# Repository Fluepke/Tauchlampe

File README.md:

Tauchlampe
==========

Die Dokumentation dieses Projektes finden Sie in der entsprechenden [Wiki](https://github.com/Fluepke/Tauchlampe/wiki)

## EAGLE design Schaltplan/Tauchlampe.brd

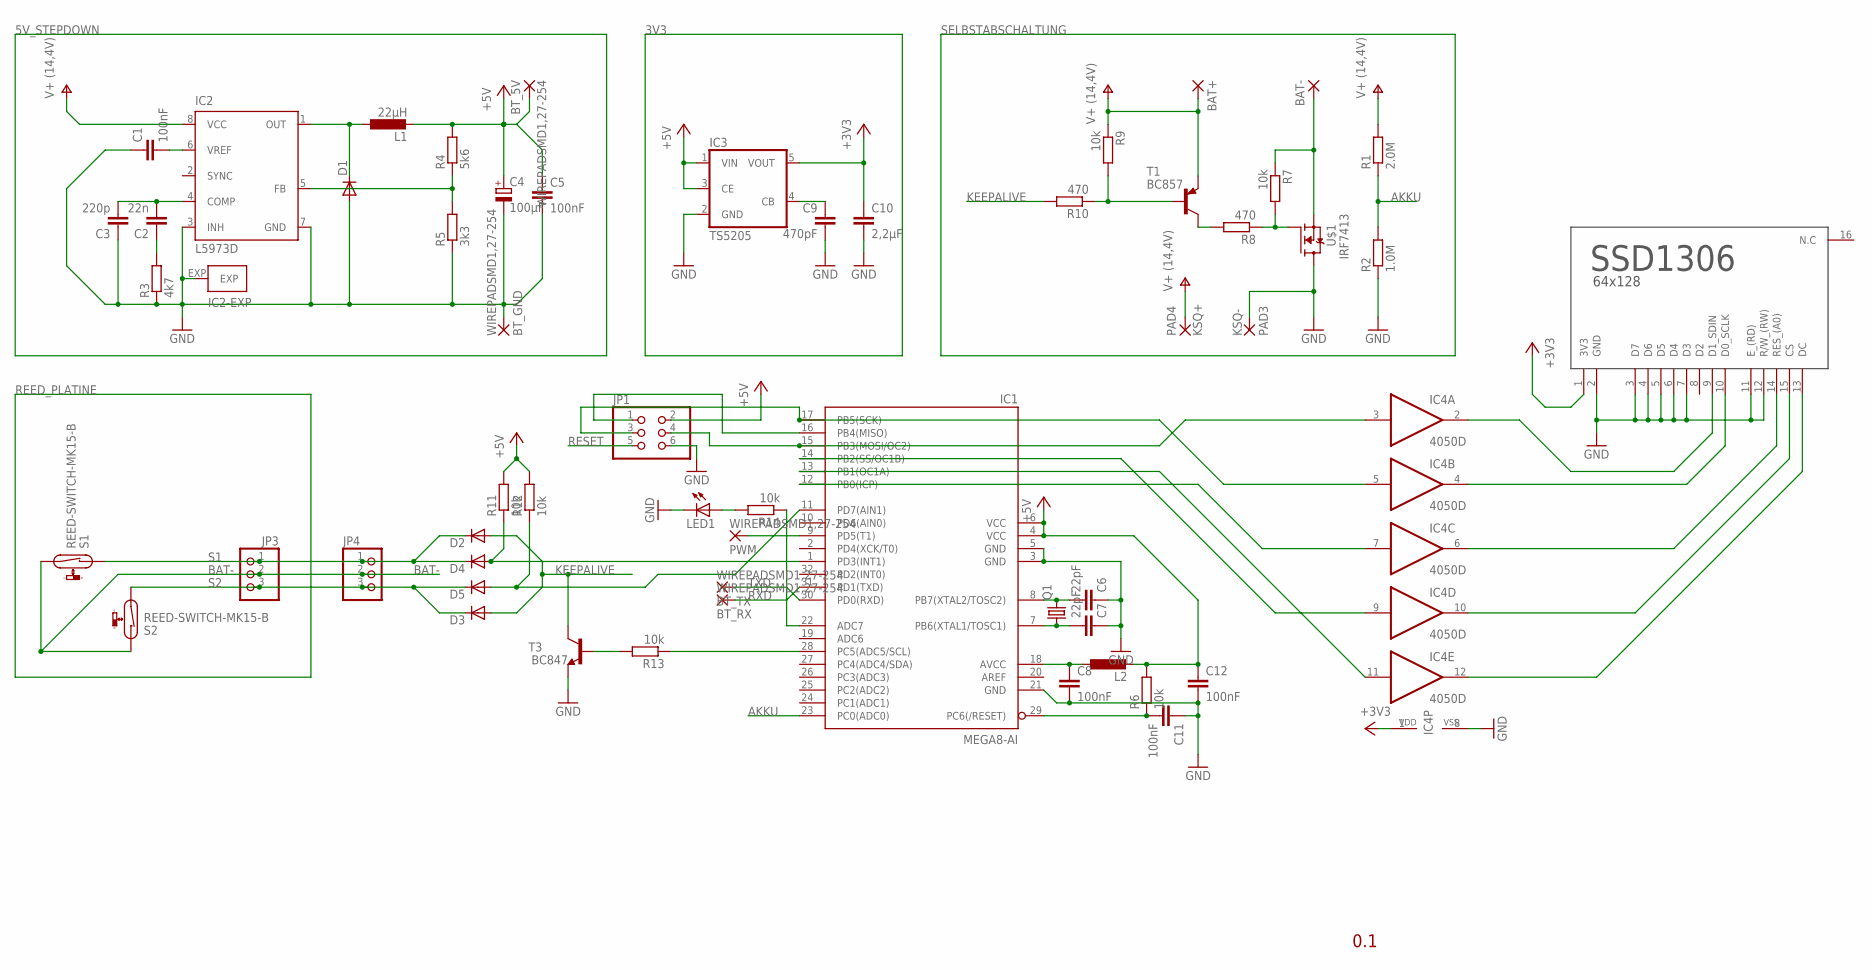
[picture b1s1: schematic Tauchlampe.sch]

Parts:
BAT+: WIREPAD3,81/1,1; 3,81/1,1
BAT-: WIREPAD3,81/1,1; 3,81/1,1
BT_5V: WIREPADSMD1,27-254; SMD1,27-2,54
BT_GND: WIREPADSMD1,27-254; SMD1,27-2,54
BT_RX: WIREPADSMD1,27-254; SMD1,27-2,54
BT_TX: WIREPADSMD1,27-254; SMD1,27-2,54
C1, C8, C11, C12: 100nF; C0603K
C2: 22n; C0603K
C3: 220p; C0603K
C4: 100µF; 153CLV-0505
C5: 100nF; C1206
C6, C7: 22pF; C1206
C9: 470pF; C0603
C10: 2,2µF; C0603
D1: DIODE-SMB; SMB
D2, D3, D4, D5: DIODE-SOD323-W; SOD323-W
IC1: MEGA8-AI; TQFP32-08
IC2: L5973D; HSOP8
IC3: TS5205; SOT25
IC4: 4050D; SO16
JP1: PINHD-2X3; 2X03
JP3, JP4: PINHD-1X03_2.54; 1X03
L1: 22µH; PISG
L2: L-EUL2012C; L2012C
LED1: LEDCHIP-LED0805; CHIP-LED0805
PAD3: KSQ-; 3,81/1,1
PAD4: KSQ+; 3,81/1,1
PWM: WIREPADSMD1,27-254; SMD1,27-2,54
Q1: CRYSTALHC49UP; HC49UP
R1: 2.0M; M1206
R2: 1.0M; M1206
R3: 4k7; R0603
R4: 5k6; R0603
R5: 3k3; R0603
R6: 10k; R1206
R7, R9, R14: 10k; M0805
R8, R10: 470; M0805
R11, R12, R13: 10k; M1206
S1, S2: REED-SWITCH-MK15-B; MK15
T1: BC857; SOT23-BEC
T3: BC847; SOT23
U$1: IRF7413; SO-8
U$2: SDD1306; 2X08

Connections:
+3V3: C10.1, IC3.5 (VOUT), IC4.1 (VDD), U$2.1 (3V3)
+5V: BT_5V.1, C4.+, C5.1, C12.1, IC1.4 (VCC), IC1.6 (VCC), IC3.1 (VIN), IC3.3 (CE), JP1.2, L1.2, L2.2, R4.2, R6.2, R11.2, R12.2
AKKU: IC1.23 (PC0(ADC0)), R1.1, R2.2
BAT-: BAT-.1, JP3.2, JP4.2, R7.1, S1.2, S2.1, U$1.1 (S), U$1.2 (S), U$1.3 (S)
CS_5V: IC1.14 (PB2(SS/OC1B)), IC4.9 (I)
D0_SCLK_5V: IC1.17 (PB5(SCK)), IC4.5 (I), JP1.3
D1_SDIN_5V: IC1.15 (PB3(MOSI/OC2)), IC4.3 (I), JP1.4
DC_5V: IC1.13 (PB1(OC1A)), IC4.11 (I)
GND: BT_GND.1, C1.1, C3.1, C4.-, C5.2, C6.1, C7.1, C8.2, C9.2, C10.2, C11.1, C12.2, D1.A, IC1.3 (GND), IC1.5 (GND), IC1.21 (GND), IC2.3 (INH), IC2.7 (GND), IC2.EXP, IC3.2 (GND), IC4.8 (VSS), JP1.6, LED1.C, PAD3.1, R2.1, R3.1, R5.1, T3.2 (E), U$1.5 (D), U$1.6 (D), U$1.7 (D), U$1.8 (D), U$2.2 (GND), U$2.3 (D7), U$2.4 (D6), U$2.5 (D5), U$2.6 (D4), U$2.7 (D3), U$2.11 (E_(RD)), U$2.12 (R/W_(RW))
KEEPALIVE: D2.A, D3.A, R10.2, T3.3 (C)
unnamed: C1.2, IC2.6 (VREF)
unnamed: D4.A, IC1.1 (PD3(INT1)), R11.1
unnamed: C2.2, C3.2, IC2.4 (COMP)
unnamed: C2.1, R3.2
unnamed: D1.C, IC2.1 (OUT), L1.1
unnamed: C6.2, IC1.8 (PB7(XTAL2/TOSC2)), Q1.2
unnamed: IC2.5 (FB), R4.1, R5.2
unnamed: C7.2, IC1.7 (PB6(XTAL1/TOSC1)), Q1.1
unnamed: R7.2, R8.1, U$1.4 (G)
unnamed: R9.2, R10.1, T1.B
unnamed: R8.2, T1.C
unnamed: D5.A, IC1.11 (PD7(AIN1)), R12.1
unnamed: R13.2, T3.1 (B)
unnamed: IC1.16 (PB4(MISO)), JP1.1
unnamed: IC1.28 (PC5(ADC5/SCL)), R13.1
unnamed: C9.1, IC3.4 (CB)
unnamed: C8.1, IC1.18 (AVCC), L2.1
unnamed: IC4.2 (O), U$2.9 (D1_SDIN)
unnamed: IC4.4 (O), U$2.10 (D0_SCLK)
unnamed: IC4.6 (O), U$2.14 (RES_(A0))
unnamed: IC4.10 (O), U$2.15 (CS)
unnamed: IC4.12 (O), U$2.13 (DC)
unnamed: IC1.9 (PD5(T1)), PWM.1
unnamed: LED1.A, R14.2
unnamed: IC1.22 (ADC7), R14.1
RESET: C11.2, IC1.29 (PC6(/RESET)), JP1.5, R6.1
RES_5V: IC1.12 (PB0(ICP)), IC4.7 (I)
RXD: BT_RX.1, IC1.31 (PD1(TXD))
S1: D2.C, D4.C, JP3.1, JP4.1, S1.1
S2: D3.C, D5.C, JP3.3, JP4.3, S2.2
TXD: BT_TX.1, IC1.30 (PD0(RXD))
V+: BAT+.1, IC2.8 (VCC), PAD4.1, R1.2, R9.1, T1.E

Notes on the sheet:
0.1

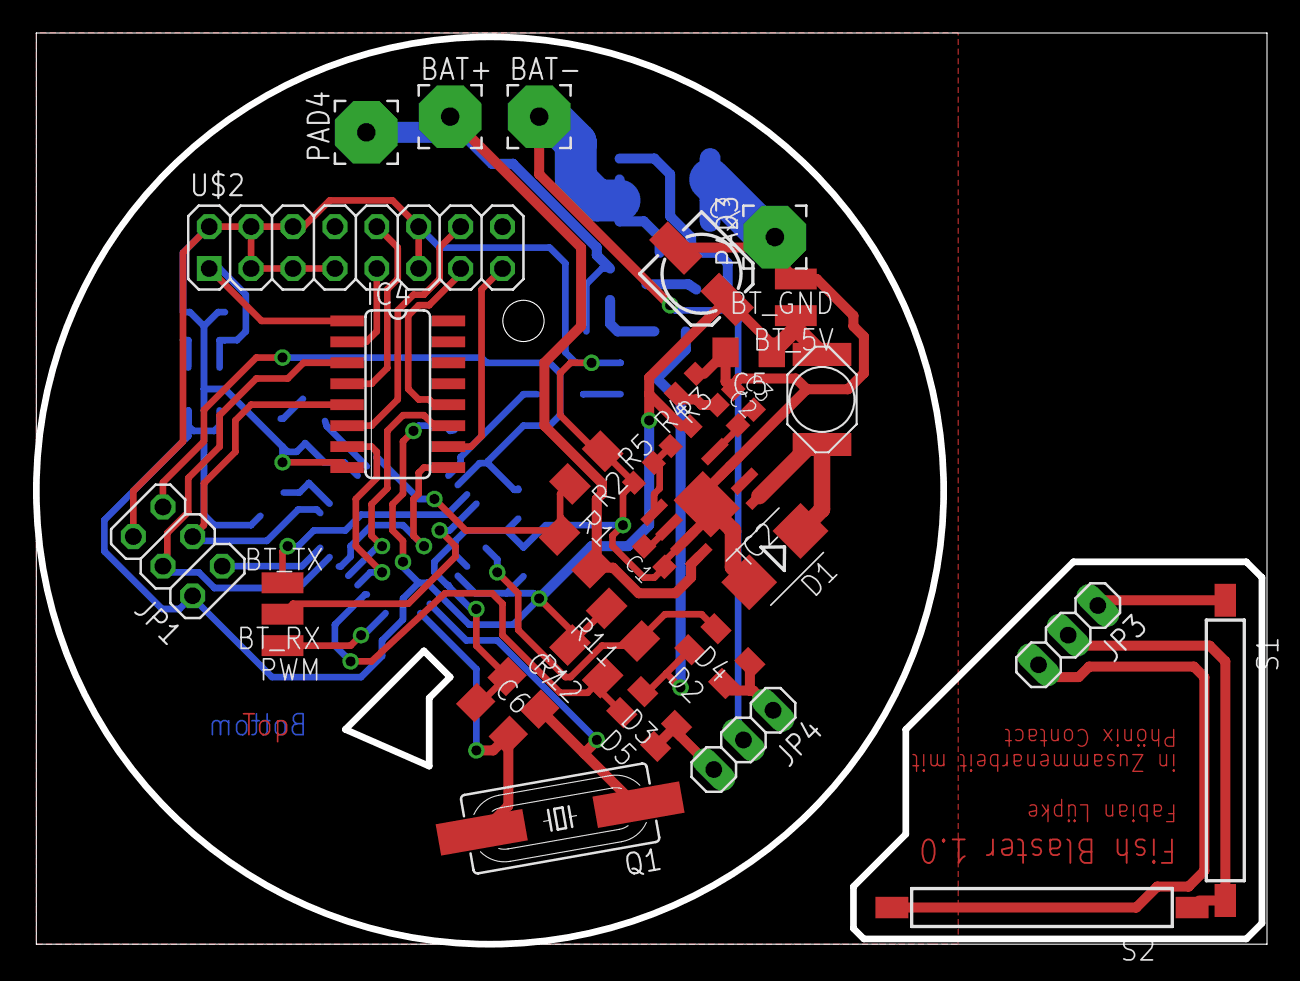
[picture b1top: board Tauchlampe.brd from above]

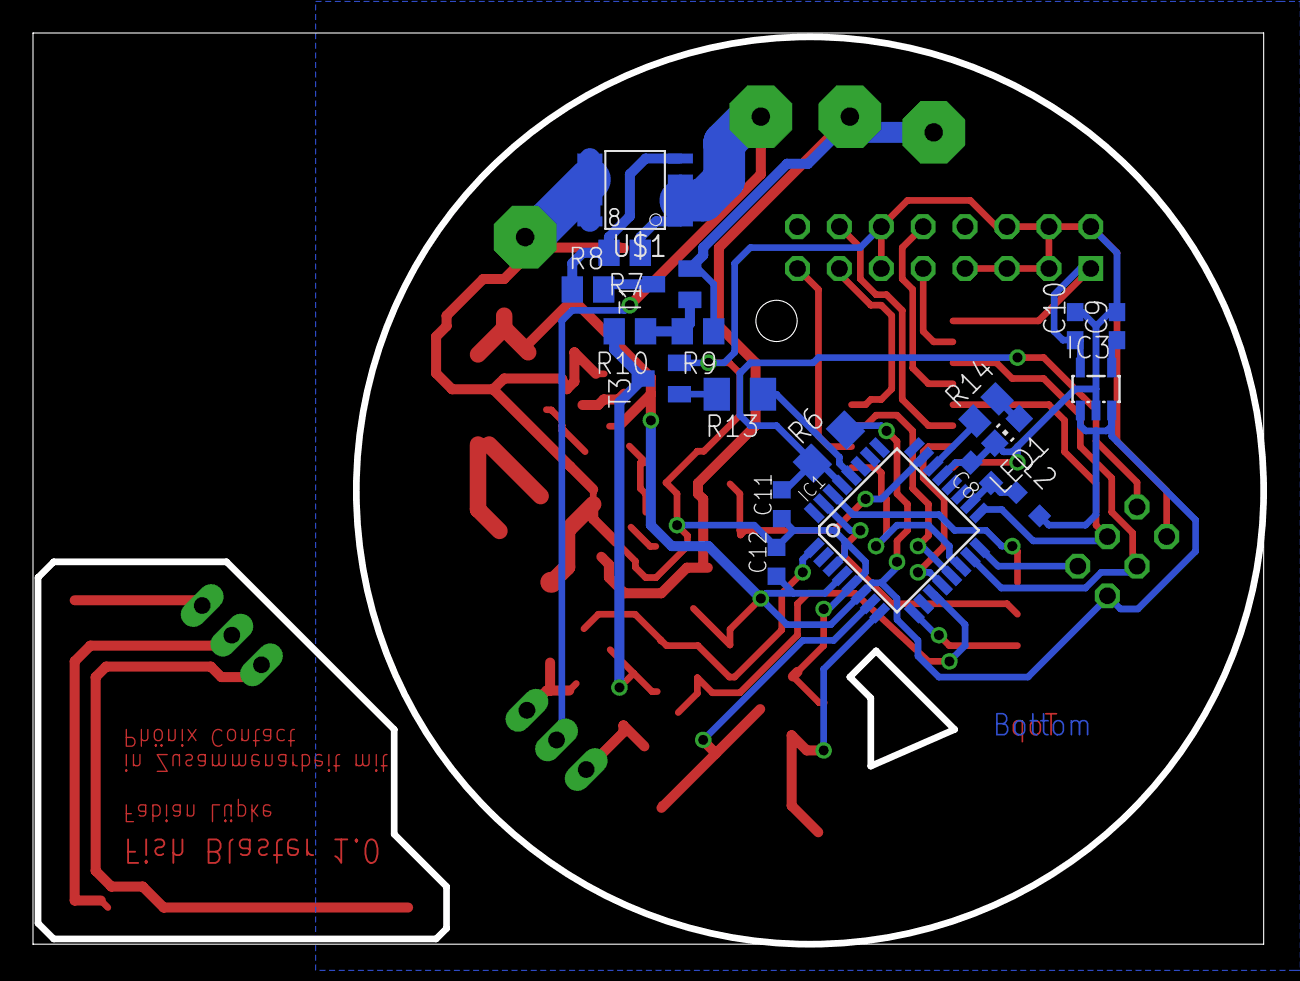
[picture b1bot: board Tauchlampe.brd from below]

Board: 2 copper layers, 74.4 x 55.0 mm, 57 parts (19 on the bottom side), 42 nets.

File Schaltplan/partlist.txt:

Partlist

Exported from Tauchlampe.sch at 26.05.14 22:14

EAGLE Version 6.5.0 Copyright (c) 1988-2013 CadSoft

Assembly variant: 

Part     Value              Device               Package      Library             Sheet

BAT+                        WIREPAD3,81/1,1      3,81/1,1     wirepad             1
BAT-                        WIREPAD3,81/1,1      3,81/1,1     wirepad             1
BT_5V    WIREPADSMD1,27-254 WIREPADSMD1,27-254   SMD1,27-2,54 wirepad             1
BT_GND   WIREPADSMD1,27-254 WIREPADSMD1,27-254   SMD1,27-2,54 wirepad             1
BT_RX    WIREPADSMD1,27-254 WIREPADSMD1,27-254   SMD1,27-2,54 wirepad             1
BT_TX    WIREPADSMD1,27-254 WIREPADSMD1,27-254   SMD1,27-2,54 wirepad             1
C1       100nF              C-EUC0603K           C0603K       rcl                 1
C2       22n                C-EUC0603K           C0603K       rcl                 1
C3       220p               C-EUC0603K           C0603K       rcl                 1
C4       100µF              CPOL-EU153CLV-0505   153CLV-0505  rcl                 1
C5       100nF              C-EUC1206            C1206        rcl                 1
C6       22pF               C-EUC1206            C1206        rcl                 1
C7       22pF               C-EUC1206            C1206        rcl                 1
C8       100nF              C-EUC0603K           C0603K       rcl                 1
C9       470pF              C-EUC0603            C0603        rcl                 1
C10      2,2µF              C-EUC0603            C0603        rcl                 1
C11      100nF              C-EUC0603K           C0603K       rcl                 1
C12      100nF              C-EUC0603K           C0603K       rcl                 1
D1                          DIODE-SMC            SMC          diode               1
D2                          DIODE-SOD323-W       SOD323-W     diode               1
D3                          DIODE-SOD323-W       SOD323-W     diode               1
D4                          DIODE-SOD323-W       SOD323-W     diode               1
D5                          DIODE-SOD323-W       SOD323-W     diode               1
IC1      MEGA8-AI           MEGA8-AI             TQFP32-08    atmel               1
IC2      L5973D             L5973D               HSOP8        st-microelectronics 1
IC3      TS5205             TS5205               SOT25        v-reg               1
IC4      4050D              4050D                SO16         40xx                1
JP1                         PINHD-2X3            2X03         pinhead             1
JP2                         PINHD-1X03_2.54-SMD  1X03SMD      pinhead-2           1
JP3                         PINHD-1X03_2.54      1X03         pinhead-2           1
L1       22µH               L-EUPISG             PISG         inductor-fastron    1
L2                          L-EUL2012C           L2012C       rcl                 1
LED1                        LEDCHIP-LED0805      CHIP-LED0805 led                 1
PAD3     KSQ-               WIREPAD3,81/1,1      3,81/1,1     wirepad             1
PAD4     KSQ+               WIREPAD3,81/1,1      3,81/1,1     wirepad             1
PWM      WIREPADSMD1,27-254 WIREPADSMD1,27-254   SMD1,27-2,54 wirepad             1
Q1                          CRYSTALHC49UP        HC49UP       crystal             1
R1       2.0M               R-EU_M1206           M1206        rcl                 1
R2       1.0M               R-EU_M1206           M1206        rcl                 1
R3       4k7                R-EU_R0603           R0603        rcl                 1
R4       5k6                R-EU_R0603           R0603        rcl                 1
R5       3k3                R-EU_R0603           R0603        rcl                 1
R6       10k                R-EU_R1206           R1206        rcl                 1
R7       10k                R-EU_M0805           M0805        rcl                 1
R8       470                R-EU_M0805           M0805        rcl                 1
R9       10k                R-EU_M0805           M0805        rcl                 1
R10      470                R-EU_M0805           M0805        rcl                 1
R11      10k                R-EU_M1206           M1206        rcl                 1
R12      10k                R-EU_M1206           M1206        rcl                 1
R13      10k                R-EU_M1206           M1206        rcl                 1
R14      10k                R-EU_M0805           M0805        rcl                 1
S1       REED-SWITCH-MK15-B REED-SWITCH-MK15-B   MK15         switch-reed         1
S2       REED-SWITCH-MK15-B REED-SWITCH-MK15-B   MK15         switch-reed         1
T1       BC857              BC857A-PNP-SOT23-BEC SOT23-BEC    transistor          1
T3       BC847              BC847                SOT23        transistor          1
U$1      IRF7413            IRF7413              SO-8         01_eigeneBauteile   1
U$2      SDD1306            SDD1306              2X08         Display-SSD1306     1

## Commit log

2014-06-10 Bilder hinzugefügt
2014-06-10 Noch mehr Bilder hinzugefügt
2014-06-10 Bild testweise verkleinert
2014-06-10 Selbstabschaltung hinzugefügt
2014-06-10 Schalterauswertung hinzugefügt
2014-06-10 Bilder vom OLED hinzugefügt
2014-06-10 Schaltplanbilder hinzugefügt
2014-06-10 5V Stepdown hinzugefügt
2014-06-10 5V Stepdown zugeschnitten
2014-06-10 Platinen hinzugefügt
2014-06-11 Schaltplan hinzugefügt
2014-06-12 Screenshot der App hinzugefügt
2014-06-12 Noch ein Foto vom Gehäuse
2014-06-13 Link zur Wiki hinzugefügt
2014-06-13 Link korrigiert
